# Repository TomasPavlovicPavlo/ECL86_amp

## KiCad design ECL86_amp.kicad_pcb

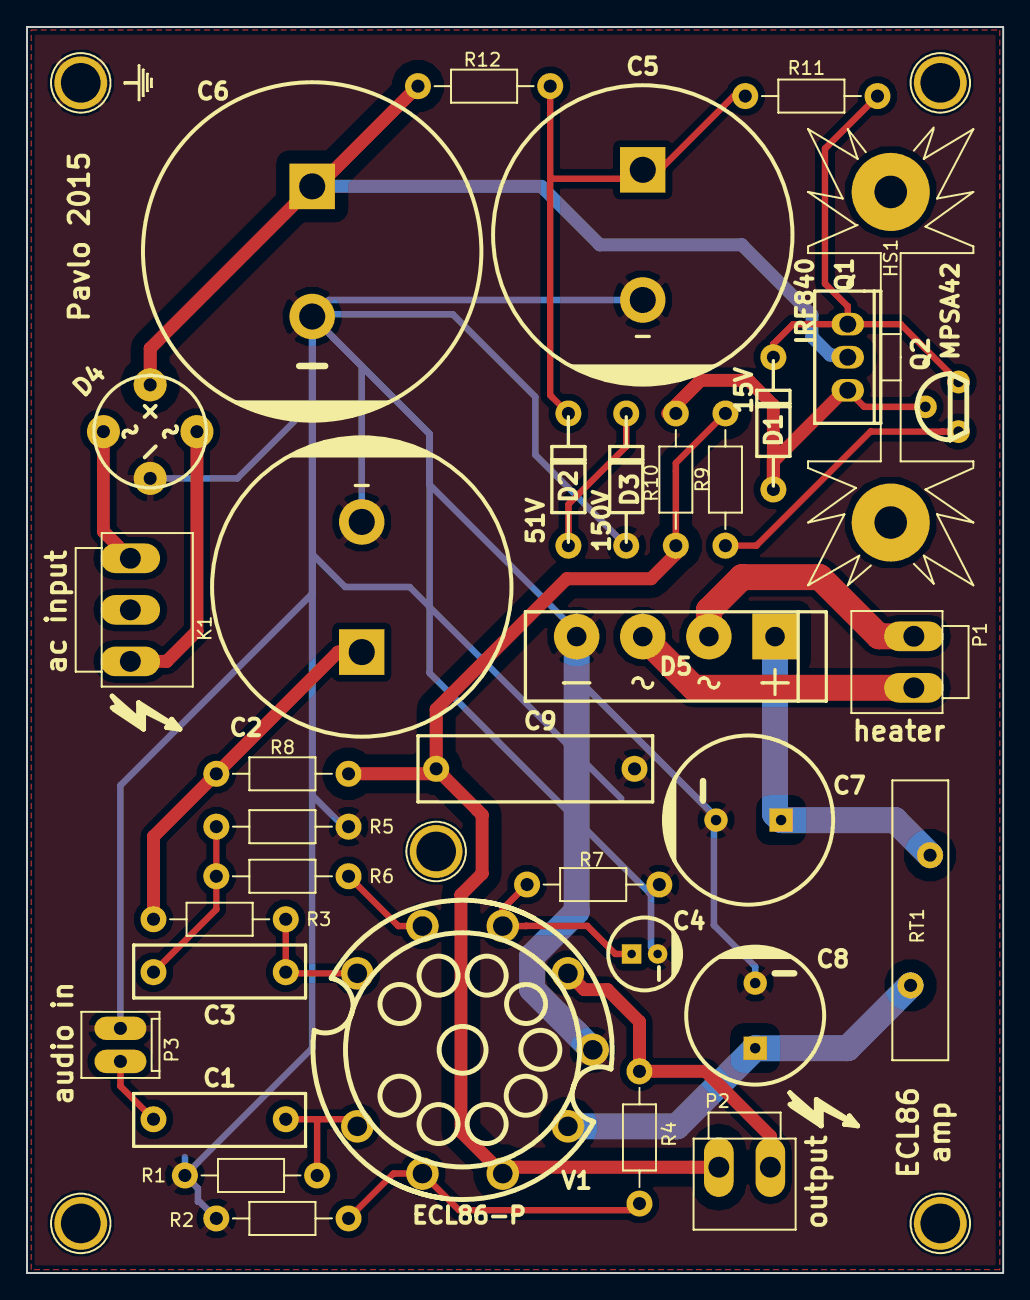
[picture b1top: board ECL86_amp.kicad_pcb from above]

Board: 2 copper layers, 75.0 x 95.7 mm, 40 parts (0 on the bottom side), 23 nets.

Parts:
C1, C3: 22n/400V; cnp_13x4mm
C2, C5: 47u/450V; CP_22x20mm
C4: 47u/25V; CP_5x11mm
C6: 100u/450V; CP_25x30mm
C7: 2200u/16V; CP_12.5x20mm
C8: 1000u/16V; CP_10x20mm
C9: 100n/400V; cnp_18x5mm
D1: 15V; diode_do41
D2: 51V; diode_do41
D3: 150V; diode_do41
D4: B250R; bridge_B25R
D5: GBU6M; bridge_GBU6M
HS1: HEATSINK; Heatsink_Fischer_SK104-STC-STIC_35x13mm_2xDrill2.5mm
K1: CONN_3; NSL39-3G
P1, P2: CONN_2; NSL39-2G
P3: CONN_2; NSL25-2G
P4, P5, P6, P7, P8: CONN_01X01; 1pin
Q1: IRF840; to220_std
Q2: MPSA42; to92_3
R1: 10M; Resistor_Horizontal_RM10mm
R2: 330; Resistor_Horizontal_RM10mm
R3, R4: 330k; Resistor_Horizontal_RM10mm
R5: 680k; Resistor_Horizontal_RM10mm
R6: 10k; Resistor_Horizontal_RM10mm
R7: 220; Resistor_Horizontal_RM10mm
R8: 4k7/1W; Resistor_Horizontal_RM10mm
R9: 100; Resistor_Horizontal_RM10mm
R10: 10; Resistor_Horizontal_RM10mm
R11: 1M; Resistor_Horizontal_RM10mm
R12: 100k; Resistor_Horizontal_RM10mm
RT1: S237/10; RV_Disc_D21.5_W4.3_P10
V1: ECL86-P; socket_gzc9-b

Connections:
/+H: C8.1, RT1.2, V1.4
/+HV: C9.2, P2.1, R8.1, R9.1, R10.1, V1.3
/+HV_UNREG: C6.1, D4.1, Q1.2, R12.2
/+H_UNREG: C7.1, D5.1, RT1.1
GND: C2.2, C4.2, C5.2, C6.2, C7.2, C8.2, C9.1, D3.2, D4.4, D5.4, P3.1, P7.1, R1.2, R2.2, R5.2, R7.2, V1.5
unnamed: C1.1, R1.1, V1.1
unnamed: C1.2, P3.2
unnamed: C2.1, R3.1, R8.2
unnamed: C3.1, R5.1, R6.2
unnamed: C3.2, R3.2, V1.9
unnamed: C4.1, R7.1, V1.7
unnamed: C5.1, D2.1, R11.2, R12.1
unnamed: D1.1, Q1.1, Q2.3, R11.1
unnamed: D1.2, Q1.3, Q2.2, R10.2
unnamed: D2.2, D3.1
unnamed: D4.2, K1.3
unnamed: D4.3, K1.1
unnamed: D5.2, P1.1
unnamed: D5.3, P1.2
unnamed: P2.2, R4.1, V1.6
unnamed: Q2.1, R9.2
unnamed: R2.1, R4.2, V1.2
unnamed: R6.1, V1.8

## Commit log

2022-01-03 001
    first upload
